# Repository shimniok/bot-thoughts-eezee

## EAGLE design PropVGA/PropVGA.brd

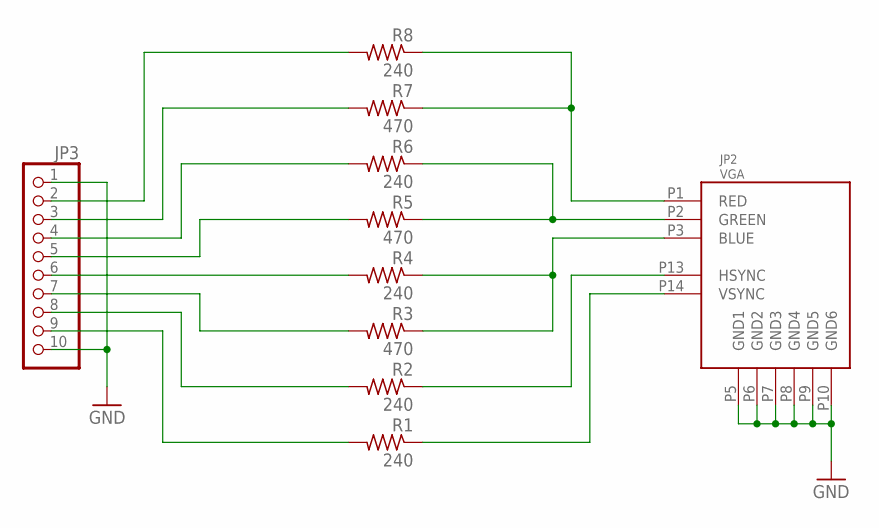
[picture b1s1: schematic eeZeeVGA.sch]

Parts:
JP2: VGA; FCI_DSUB_HD_15_RA
JP3: PINHD-1X10_2.54-S; 1X10-S
R1, R2, R4, R6, R8: 240; R0603
R3, R5, R7: 470; R0603

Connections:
B: JP2.P3 (BLUE), R3.1, R4.1
G: JP2.P2 (GREEN), R5.1, R6.1
GND: JP2.P5 (GND1), JP2.P6 (GND2), JP2.P7 (GND3), JP2.P8 (GND4), JP2.P9 (GND5), JP2.P10 (GND6), JP3.1, JP3.10
H: JP2.P13 (HSYNC), R2.1
unnamed: JP3.9, R1.2
unnamed: JP3.8, R2.2
unnamed: JP3.7, R3.2
unnamed: JP3.6, R4.2
unnamed: JP3.5, R5.2
unnamed: JP3.4, R6.2
unnamed: JP3.3, R7.2
unnamed: JP3.2, R8.2
R: JP2.P1 (RED), R7.1, R8.1
V: JP2.P14 (VSYNC), R1.1

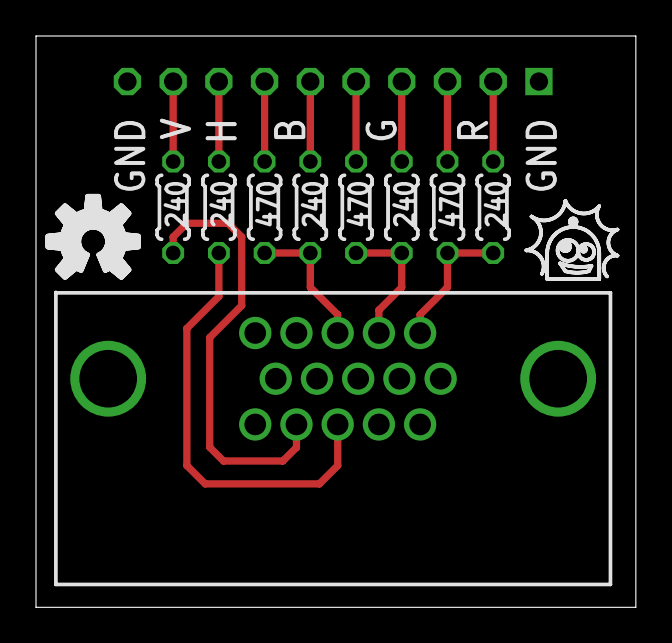
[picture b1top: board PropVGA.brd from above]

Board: 2 copper layers, 33.3 x 31.7 mm, 10 parts (1 on the bottom side), 14 nets.

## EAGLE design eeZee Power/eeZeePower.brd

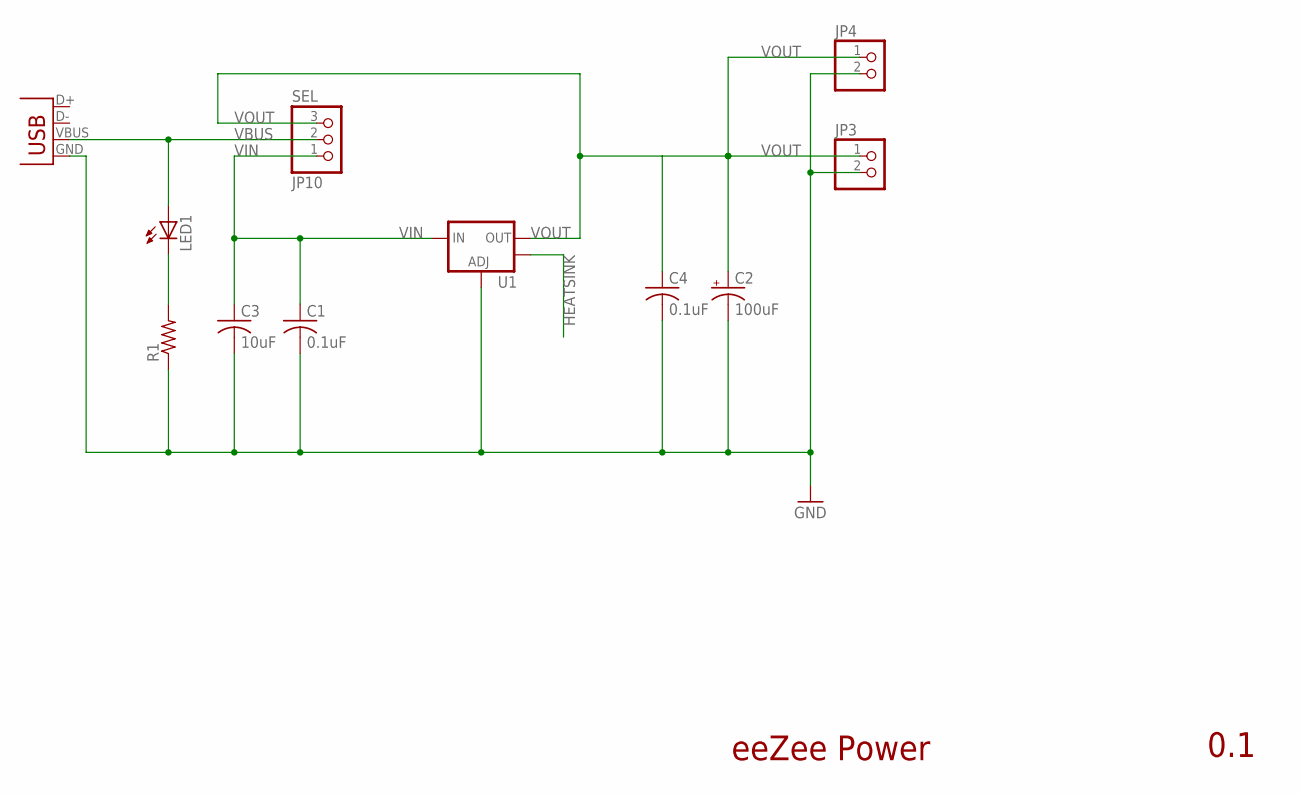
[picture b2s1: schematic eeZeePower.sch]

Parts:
C1, C4: 0.1uF; C0603
C2: 100uF; SMC_B
C3: 10uF; C0603
JP1: USBSMD; USB-MINIB
JP3, JP4: PINHD-1X02_2.54-S; 1X02-S
JP10: SEL; 1X03-S
LED1: LEDCHIPLED_0805; CHIPLED_0805
R1: R-US_R0603; R0603
U1: V_REG_LM1117SOT223; SOT223

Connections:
GND: C1.2, C2.-, C3.2, C4.2, JP1.GND, JP3.2, JP4.2, R1.1, U1.1 (ADJ)
HEATSINK: U1.4 (OUT)
unnamed: LED1.C, R1.2
VBUS: JP1.VBUS, JP10.2, LED1.A
VIN: C1.1, C3.1, JP10.1, U1.3 (IN)
VOUT: C2.+, C4.1, JP3.1, JP4.1, JP10.3, U1.2 (OUT)

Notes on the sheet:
eeZee Power
0.1

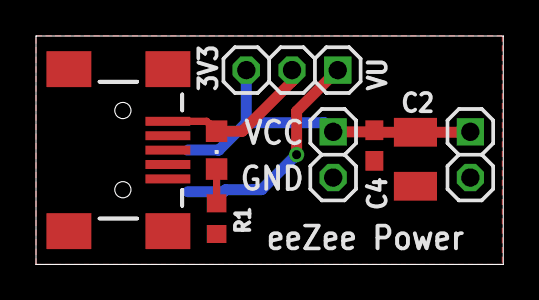
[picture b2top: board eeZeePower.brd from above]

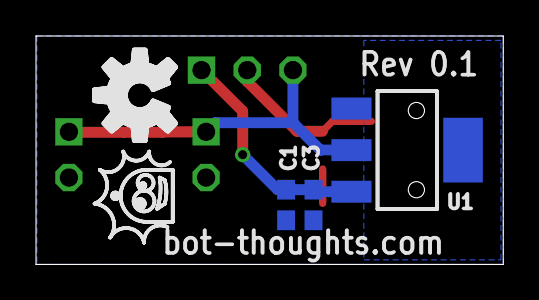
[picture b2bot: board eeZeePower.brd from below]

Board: 2 copper layers, 26.0 x 12.7 mm, 11 parts (3 on the bottom side), 5 nets.

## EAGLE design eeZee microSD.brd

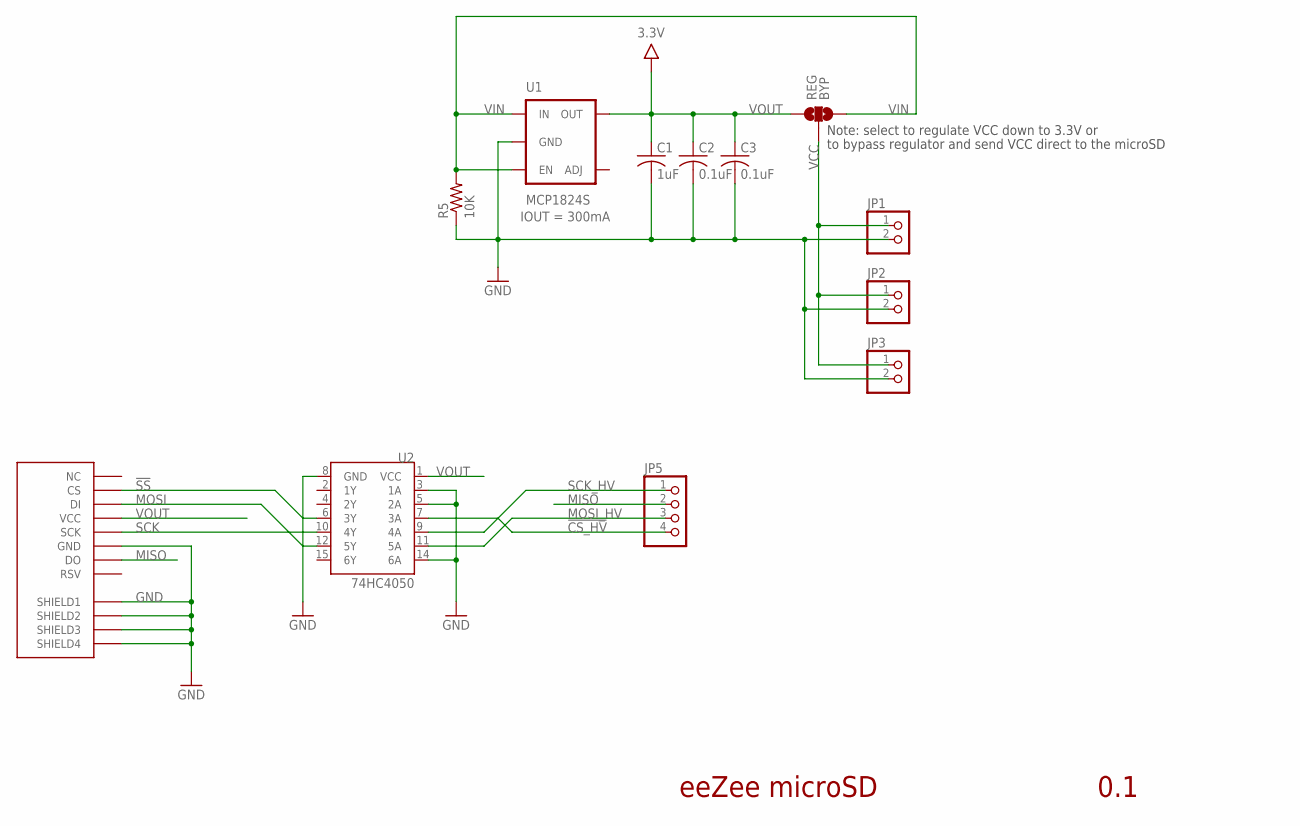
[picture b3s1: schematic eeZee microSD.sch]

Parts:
C1: 1uF; C0603; PARTNO LMK107B7105KA-T
C2, C3: 0.1uF; C0603; PARTNO LMK107B7105KA-T
JP1, JP2, JP3: PINHD-1X02_2.54-S; 1X02-S
JP5: PINHD-1X04_2.54-S; 1X04-S
R5: 10K; R0603; PARTNO ERJ-3GEYJ103V
REG: BYP; SJ_3
U1: MCP1824S; SOT23-5; PARTNO MCP1824ST-3302E/DB
U2: 74HC4050; SO016
U$1: MICROSD_TFLASH; TFLASH_CP-0000-086

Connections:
!CS_HV: JP5.4, U2.7 (3A)
!SS: U2.6 (3Y), U$1.CS
GND: C1.2, C2.2, C3.2, JP1.2, JP2.2, JP3.2, R5.1, U1.2 (GND), U2.3 (1A), U2.5 (2A), U2.8 (GND), U2.14 (6A), U$1.GND, U$1.SHIELD1, U$1.SHIELD2, U$1.SHIELD3, U$1.SHIELD4
MISO: JP5.2, U$1.DO
MOSI: U2.12 (5Y), U$1.DI
MOSI_HV: JP5.3, U2.11 (5A)
SCK: U2.10 (4Y), U$1.SCLK (SCK)
SCK_HV: JP5.1, U2.9 (4A)
VCC: JP1.1, JP2.1, JP3.1, REG.2
VIN: R5.2, REG.3, U1.1 (IN), U1.3 (EN)
VOUT: C1.1, C2.1, C3.1, REG.1, U1.5 (OUT), U2.1 (VCC), U$1.VDD (VCC)

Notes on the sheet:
Note: select to regulate VCC down to 3.3V or
to bypass regulator and send VCC direct to the microSD
eeZee microSD
0.1

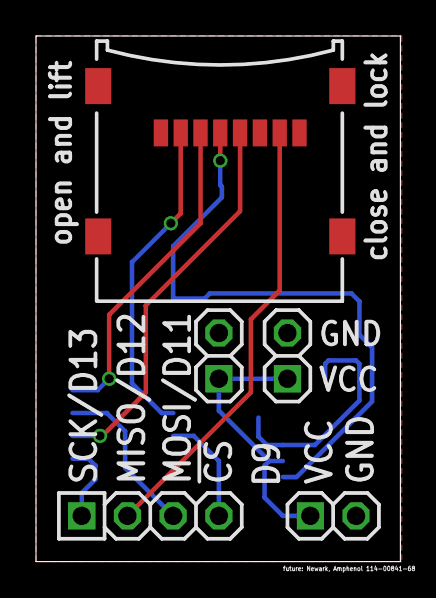
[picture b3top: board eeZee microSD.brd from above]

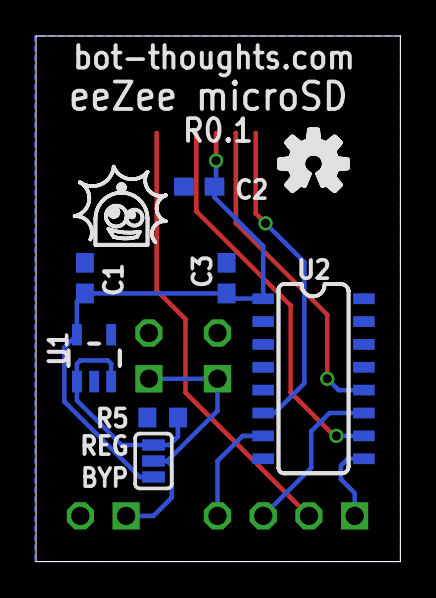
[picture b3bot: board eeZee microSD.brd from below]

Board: 2 copper layers, 20.2 x 29.2 mm, 12 parts (7 on the bottom side), 11 nets.

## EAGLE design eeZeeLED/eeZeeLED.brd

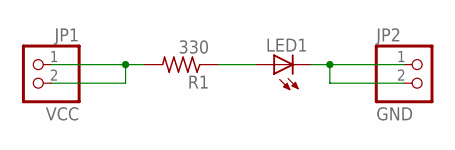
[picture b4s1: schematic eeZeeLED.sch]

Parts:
JP1: VCC; 1X02-S
JP2: GND; 1X02-S
LED1: LEDCHIPLED_0805; CHIPLED_0805
R1: 330; R0603

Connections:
unnamed: LED1.A, R1.1
unnamed: JP2.1, JP2.2, LED1.C
unnamed: JP1.1, JP1.2, R1.2

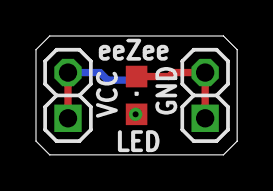
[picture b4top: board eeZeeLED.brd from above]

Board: 2 copper layers, 11.2 x 6.6 mm, 4 parts (1 on the bottom side), 3 nets.

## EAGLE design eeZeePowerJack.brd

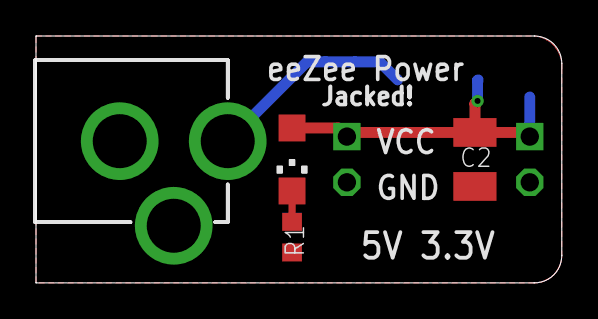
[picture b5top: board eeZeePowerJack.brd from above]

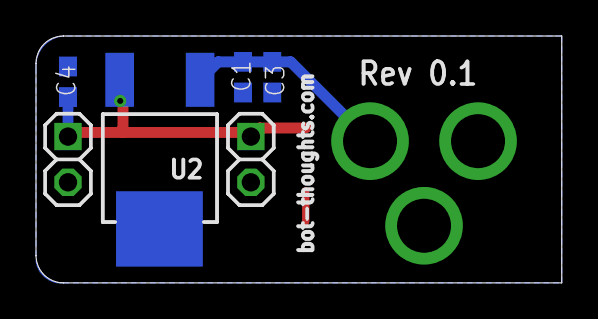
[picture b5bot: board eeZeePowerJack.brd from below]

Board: 2 copper layers, 29.2 x 13.7 mm, 10 parts (6 on the bottom side), 4 nets.

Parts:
C1, C4: 0.1uF; C0603
C2: 100uF; SMC_B
C3: 10uF; C0603
J1: POWER_JACKPTH; POWER_JACK_PTH
JP3, JP4: 1X02-S
LED1: CHIPLED_1206
R1: R0603
U2: LD29150DT; DPAK

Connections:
GND: C1.2, C2.-, C3.2, C4.2, J1.GND, J1.GNDBREAK, JP3.2, JP4.2, R1.1, U2.4
unnamed: LED1.C, R1.2
VIN: C1.1, C3.1, J1.PWR, U2.1
VOUT: C2.+, C4.1, JP3.1, JP4.1, LED1.A, U2.3

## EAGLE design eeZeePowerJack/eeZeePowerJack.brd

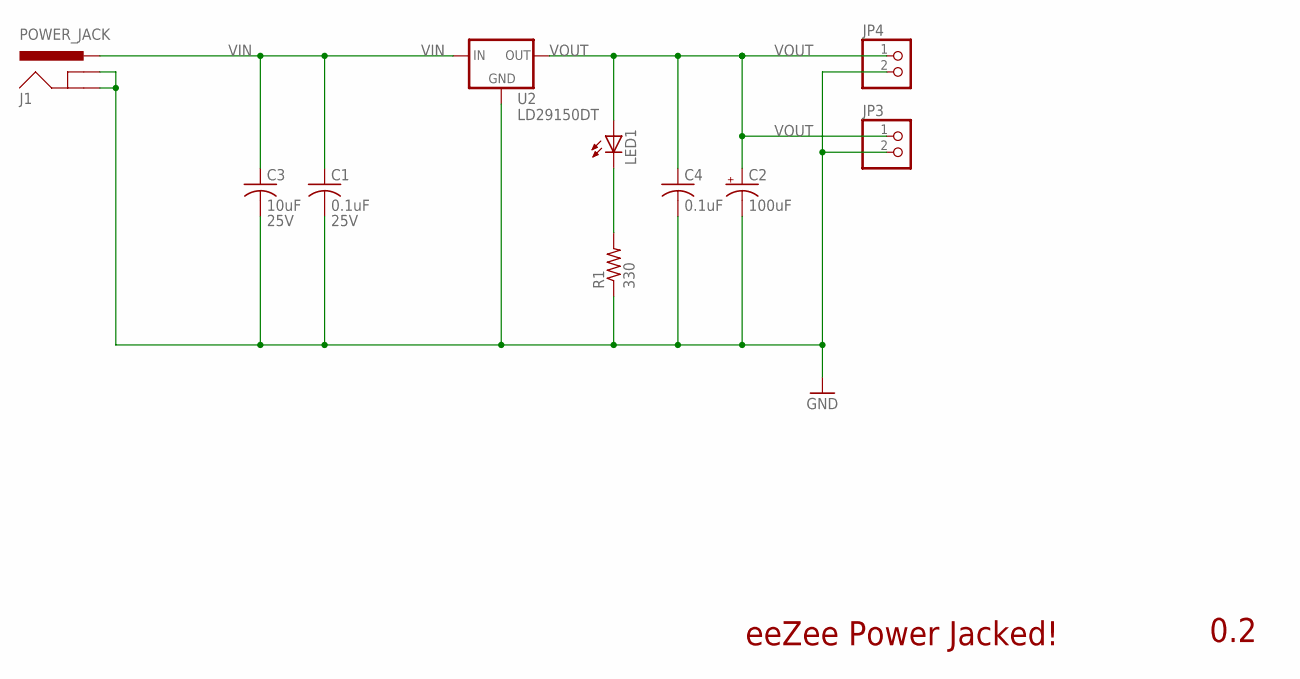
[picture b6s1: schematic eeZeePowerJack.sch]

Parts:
C1: 0.1uF; C0603; VOLTAGE 25V
C2: 100uF; SMC_B
C3: 10uF; C1206; VOLTAGE 25V
C4: 0.1uF; C0603
J1: POWER_JACK; POWER_JACK_PTH
JP3, JP4: PINHD-1X02_2.54-S; 1X02-S
LED1: LEDCHIPLED_1206; CHIPLED_1206
R1: 330; R0603
U2: LD29150DT; DPAK

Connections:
GND: C1.2, C2.-, C3.2, C4.2, J1.GND, J1.GNDBREAK, JP3.2, JP4.2, R1.1, U2.4 (GND); also elsewhere on the board
unnamed: LED1.C, R1.2
VIN: C1.1, C3.1, J1.PWR, U2.1 (VIN); also elsewhere on the board
VOUT: C2.+, C4.1, JP3.1, JP4.1, LED1.A, U2.3 (VOUT); also elsewhere on the board

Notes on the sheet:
eeZee Power Jacked!
0.2

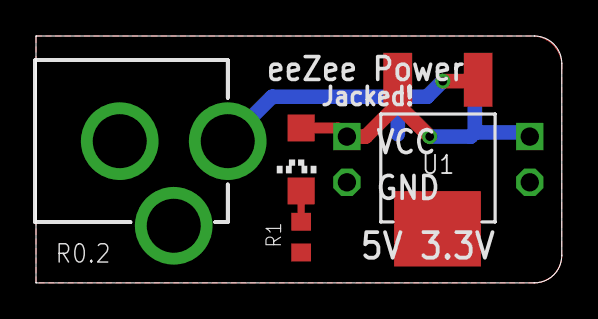
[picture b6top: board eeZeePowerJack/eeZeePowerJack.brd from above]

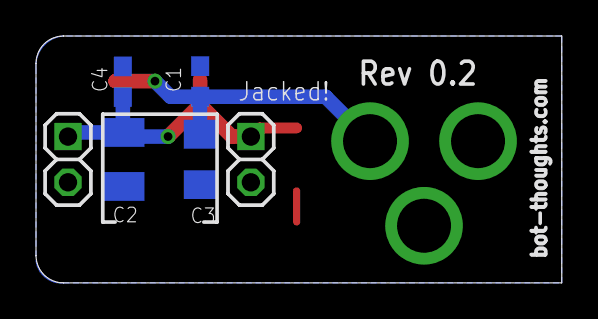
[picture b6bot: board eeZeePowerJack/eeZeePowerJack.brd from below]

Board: 2 copper layers, 29.2 x 13.7 mm, 10 parts (6 on the bottom side), 4 nets.

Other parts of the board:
U1: LF50CDT; DPAK

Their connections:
GND: U1.4; also elsewhere on the board
VIN: U1.1; also elsewhere on the board
VOUT: U1.3; also elsewhere on the board

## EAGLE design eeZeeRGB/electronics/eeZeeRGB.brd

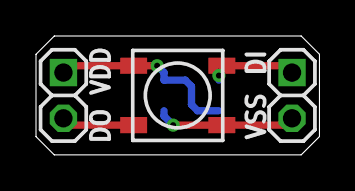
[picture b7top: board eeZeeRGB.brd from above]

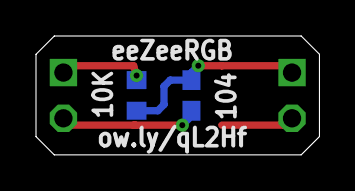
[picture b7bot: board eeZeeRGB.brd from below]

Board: 2 copper layers, 15.7 x 6.6 mm, 5 parts (2 on the bottom side), 4 nets.

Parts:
C1: 104; C0603
JP1, JP2: 1X02-S
LED1: WS2812B
R1: 10K; R0603

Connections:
DIN: JP2.1, LED1.DIN, R1.1
DOUT: JP1.2, LED1.DOUT
GND: C1.2, JP2.2, LED1.VSS
VDD: C1.1, JP1.1, LED1.VDD, R1.2

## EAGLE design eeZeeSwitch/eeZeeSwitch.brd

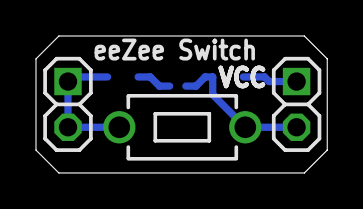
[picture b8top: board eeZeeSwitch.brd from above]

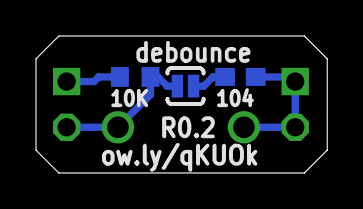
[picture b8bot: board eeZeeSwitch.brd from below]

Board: 2 copper layers, 16.2 x 7.6 mm, 6 parts (3 on the bottom side), 4 nets.

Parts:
C1: 104; C0603
JP1, JP2: 1X02-S
R1: 10K; R0603
S1: eeZee Switch; 6MMTACTILE_RECT
SJ1: debounce; SJ_2S-NO

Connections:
unnamed: JP1.2, R1.1, S1.P$2, SJ1.2
unnamed: C1.2, JP2.1, JP2.2, S1.P$1
unnamed: JP1.1, R1.2
unnamed: C1.1, SJ1.1

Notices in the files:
parts and their libraries:
SparkFun: Licensing: CC v3.0 Share-Alike You are welcome to use this library for commercial purposes.
